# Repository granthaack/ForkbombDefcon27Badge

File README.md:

# ForkbombDefcon27Badge
A badge for Defcon27 in 2019

Brainstorming on the wiki

https://github.com/granthaack/ForkbombDefcon27Badge/wiki

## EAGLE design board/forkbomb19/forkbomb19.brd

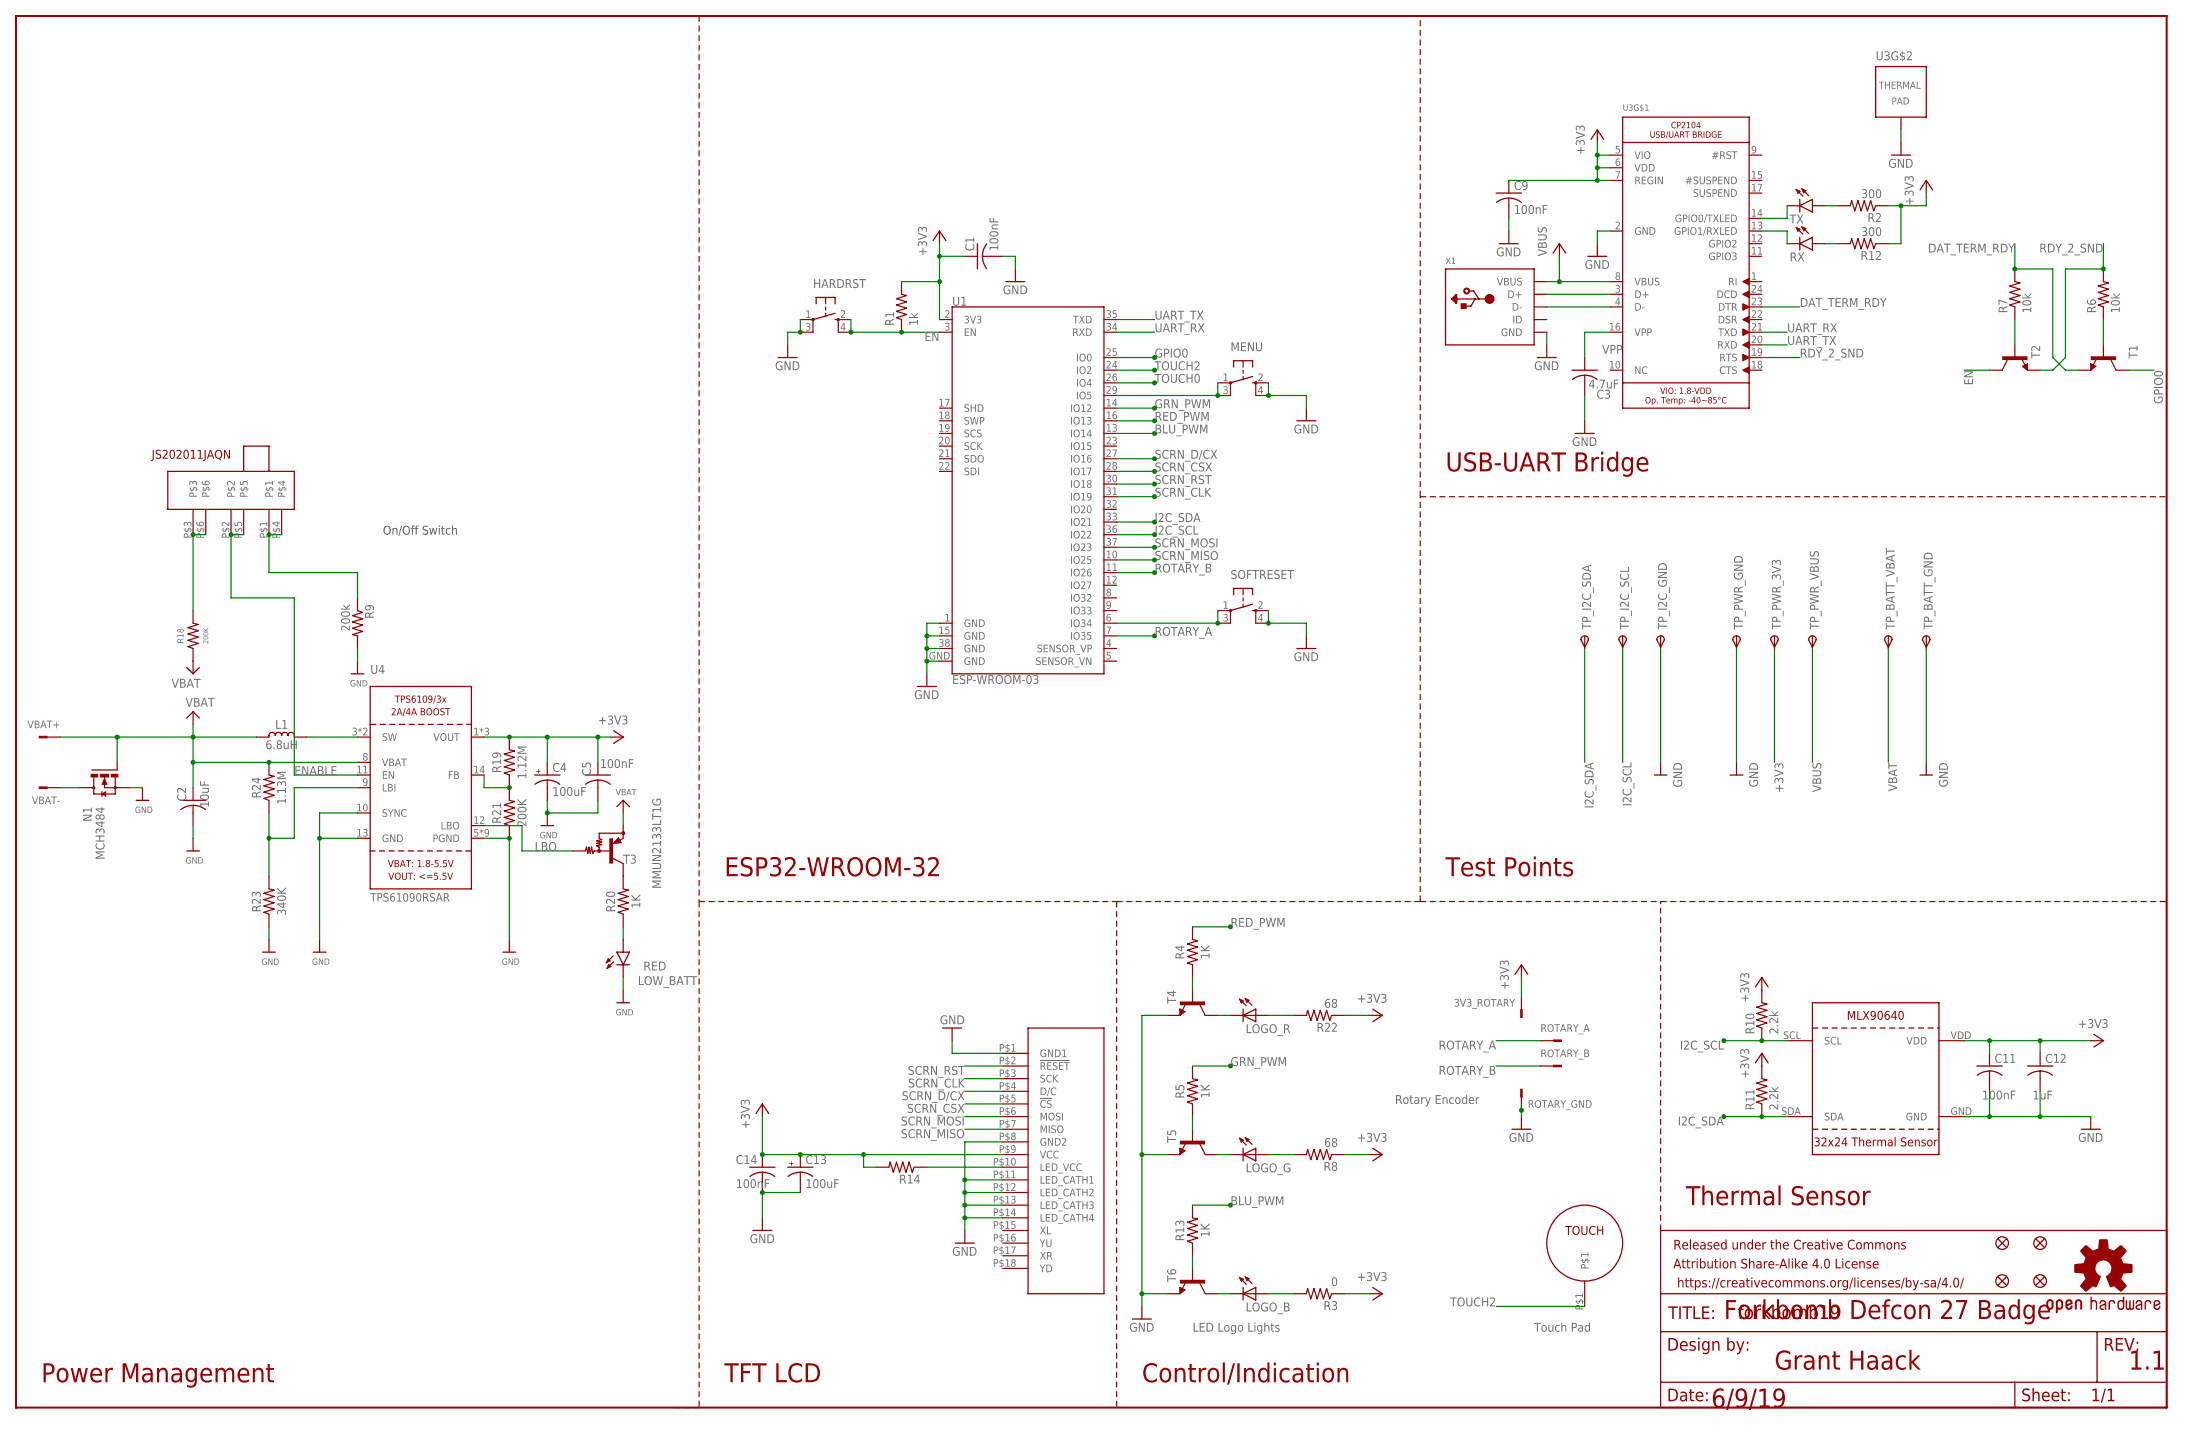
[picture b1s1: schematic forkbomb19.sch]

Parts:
3V3_ROTARY: POT_GND; TSW-101-XX-G-S
C1, C5, C9, C11, C14: 100nF; C0603
C2: 10uF; C1210
C3: 4.7uF; C0805
C4, C13: 100uF; C/6032-28R
C12: 1uF; C0805
FID1, FID2, FID3, FID4: FIDUCIAL_1MM
FRAME1: FRAME-LEDGER; CREATIVE_COMMONS
HARDRST: SPST_TACT-KMR2; KMR2
L1: 6.8uH; INDUCTOR_5X5MM_TDK_VLC5045
LOGO1: OSHW-LOGOS-COPPER; OSHW-LOGO-S_COPPER
LOGO_B: REVERSE_PLCC_LED; PLCC2_LED
LOGO_G: REVERSE_PLCC_LED; PLCC2_LED
LOGO_R: REVERSE_PLCC_LED; PLCC2_LED
LOW_BATT: RED; CHIP-LED0603
MENU: SPST_TACT-KMR2; KMR2
N1: MCH3484
R1: 1k; R0603
R2, R12: 300; R0603
R3: 0; R0805
R4, R5, R13, R20: 1K; R0603
R6, R7: 10k; R0603
R8, R22: 68; R0805
R9: 200k; R0603
R10, R11: 2.2k; R0603
R14: R-US_R1210; R1210
R18, R21: 200K; R0603
R19: 1.12M; R0603
R23: 340K; R0603
R24: 1.13M; R0603
ROTARY_A: POT_SIG; TSW-101-XX-G-S
ROTARY_B: POT_3V3; TSW-101-XX-G-S
ROTARY_GND: POT_GND; TSW-101-XX-G-S
RX: LEDCHIP-LED0603; CHIP-LED0603
SOFTRESET: SPST_TACT-KMR2; KMR2
T1, T2, T4, T5, T6: MMBT3904LT1-NPN-SOT23-BEC; SOT23-BEC
T3: MMUN2133LT1G; SC59-BEC
TOUCH: TOUCHPADTOUCH_BLANK; TOUCH_BLANK
TP_BATT_GND: TPSTP20SQ; TP20SQ
TP_BATT_VBAT: TPSTP20SQ; TP20SQ
TP_I2C_GND, TP_I2C_SCL, TP_I2C_SDA: TPSTP20SQ; TP20SQ
TP_PWR_3V3: TPSTP20SQ; TP20SQ
TP_PWR_GND: TPSTP20SQ; TP20SQ
TP_PWR_VBUS: TPSTP20SQ; TP20SQ
TX: LEDCHIP-LED0603; CHIP-LED0603
U1: ESP-WROOM-03
U3: CP2104; QFN24_4MM_SMSC
U4: TPS61090RSAR; PVQFN-16
U$2: SPI_TFT
U$7: MLX90640
U$8: JS202011JAQN
VBAT+: POT_GND; TSW-101-XX-G-S
VBAT-: POT_GND; TSW-101-XX-G-S
X1: USB_MICRO_20329_V2; 4UCONN_20329_V2

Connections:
+3V3: 3V3_ROTARY.1, C1.1, C4.+, C5.1, C9.1, C11.1, C12.1, C13.+, C14.1, R1.2, R2.1, R3.1, R8.1, R10.2, R11.2, R12.1, R14.2, R19.2, R22.1, TP_PWR_3V3.TP, U1.2 (3V3), U3.5 (VIO), U3.6 (VDD), U3.7 (REGIN), U4.1 (VOUT), U4.15 (VOUT), U4.16 (VOUT), U$2.P$9 (VCC), U$7.VDD
BLU_PWM: R13.2, U1.13 (IO14)
DAT_TERM_RDY: R7.2, T1.E, U3.23 (DTR)
EN: HARDRST.2 (S), HARDRST.4 (S1), R1.1, T2.C, U1.3 (EN)
ENABLE: U4.11 (EN), U$8.P$2, U$8.P$5
GND: C1.2, C2.2, C3.2, C4.-, C5.2, C9.2, C11.2, C12.2, C13.-, C14.2, HARDRST.1, HARDRST.3 (P1), LOW_BATT.C, MENU.2 (S), MENU.4 (S1), N1.S, R9.2, R21.1, R23.1, ROTARY_GND.1, SOFTRESET.2 (S), SOFTRESET.4 (S1), T4.E, T5.E, T6.E, TP_BATT_GND.TP, TP_I2C_GND.TP, TP_PWR_GND.TP, U1.1 (GND), U1.15 (GND), U1.38 (GND), U1.GND, U3.2 (GND), U3.THERM (TP), U4.5 (PGND), U4.6 (PGND), U4.7 (PGND), U4.10 (SYNC), U4.13 (GND), U4.P$18 (PGND), U4.P$19 (PGND), U4.P$20 (PGND), U4.P$21 (PGND), U4.P$22 (PGND), U4.THERMAL (PGND), U$2.P$1 (GND1), U$2.P$8 (GND2), U$2.P$11 (LED_CATH1), U$2.P$12 (LED_CATH2), U$2.P$13 (LED_CATH3), U$2.P$14 (LED_CATH4), U$7.GND, X1.BASE@1 (GND), X1.BASE@2 (GND), X1.GND, X1.SPRT@1 (GND), X1.SPRT@2 (GND), X1.SPRT@3 (GND), X1.SPRT@4 (GND)
GPIO0: T1.C, U1.25 (IO0)
GRN_PWM: R5.2, U1.14 (IO12)
I2C_SCL: R10.1, TP_I2C_SCL.TP, U1.36 (IO22), U$7.SCL
I2C_SDA: R11.1, TP_I2C_SDA.TP, U1.33 (IO21), U$7.SDA
LBO: T3.B, U4.12 (LBO)
MENU: MENU.1, MENU.3 (P1), U1.29 (IO5)
unnamed: R14.1, U$2.P$10 (LED_VCC)
unnamed: SOFTRESET.1, SOFTRESET.3 (P1), U1.6 (IO34)
unnamed: R18.2, U$8.P$3, U$8.P$6
unnamed: LOGO_B.2 (C), T6.C
unnamed: U3.3 (D+), X1.D+
unnamed: U3.4 (D-), X1.D-
unnamed: LOGO_B.1 (A), R3.2
unnamed: LOGO_G.2 (C), T5.C
unnamed: LOGO_R.2 (C), T4.C
unnamed: R5.1, T5.B
unnamed: R13.1, T6.B
unnamed: LOGO_R.1 (A), R22.2
unnamed: R9.1, U$8.P$1, U$8.P$4
unnamed: R4.1, T4.B
unnamed: R7.1, T2.B
unnamed: L1.P$2 (2), U4.3 (SW), U4.4 (SW)
unnamed: R6.1, T1.B
unnamed: N1.D, VBAT-.1
unnamed: RX.C, U3.13 (GPIO1/RXLED)
unnamed: TX.C, U3.14 (GPIO0/TXLED)
unnamed: R2.2, TX.A
unnamed: R12.2, RX.A
unnamed: R23.2, R24.1, U4.9 (LBI)
unnamed: LOW_BATT.A, R20.1
unnamed: R19.1, R21.2, U4.14 (FB)
unnamed: R20.2, T3.C
unnamed: LOGO_G.1 (A), R8.2
RDY_2_SND: R6.2, T2.E, U3.19 (RTS)
RED_PWM: R4.2, U1.16 (IO13)
ROTARY_A: ROTARY_A.1, U1.7 (IO35)
ROTARY_B: ROTARY_B.1, U1.11 (IO26)
SCRN_CLK: U1.31 (IO19), U$2.P$3 (SCK)
SCRN_CSX: U1.28 (IO17), U$2.P$5 (!CS)
SCRN_D/CX: U1.27 (IO16), U$2.P$4 (D/C)
SCRN_MISO: U1.10 (IO25), U$2.P$7 (MISO)
SCRN_MOSI: U1.37 (IO23), U$2.P$6 (MOSI)
SCRN_RST: U1.30 (IO18), U$2.P$2 (!RESET)
TOUCH0: U1.26 (IO4)
TOUCH2: TOUCH.P$1, U1.24 (IO2)
UART_RX: U1.34 (RXD), U3.21 (TXD)
UART_TX: U1.35 (TXD), U3.20 (RXD)
VBAT: C2.1, L1.P$1 (1), N1.G, R18.1, R24.2, T3.E, TP_BATT_VBAT.TP, U4.8 (VBAT), VBAT+.1
VBUS: TP_PWR_VBUS.TP, U3.8 (VBUS), X1.VBUS
VPP: C3.1, U3.16 (VPP)

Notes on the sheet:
On/Off Switch
Power Management
TFT LCD
Thermal Sensor
ESP32-WROOM-32
USB-UART Bridge
Control/Indication
Forkbomb Defcon 27 Badge
Grant Haack
6/9/19
1.1
LED Logo Lights
Touch Pad
Rotary Encoder
Test Points

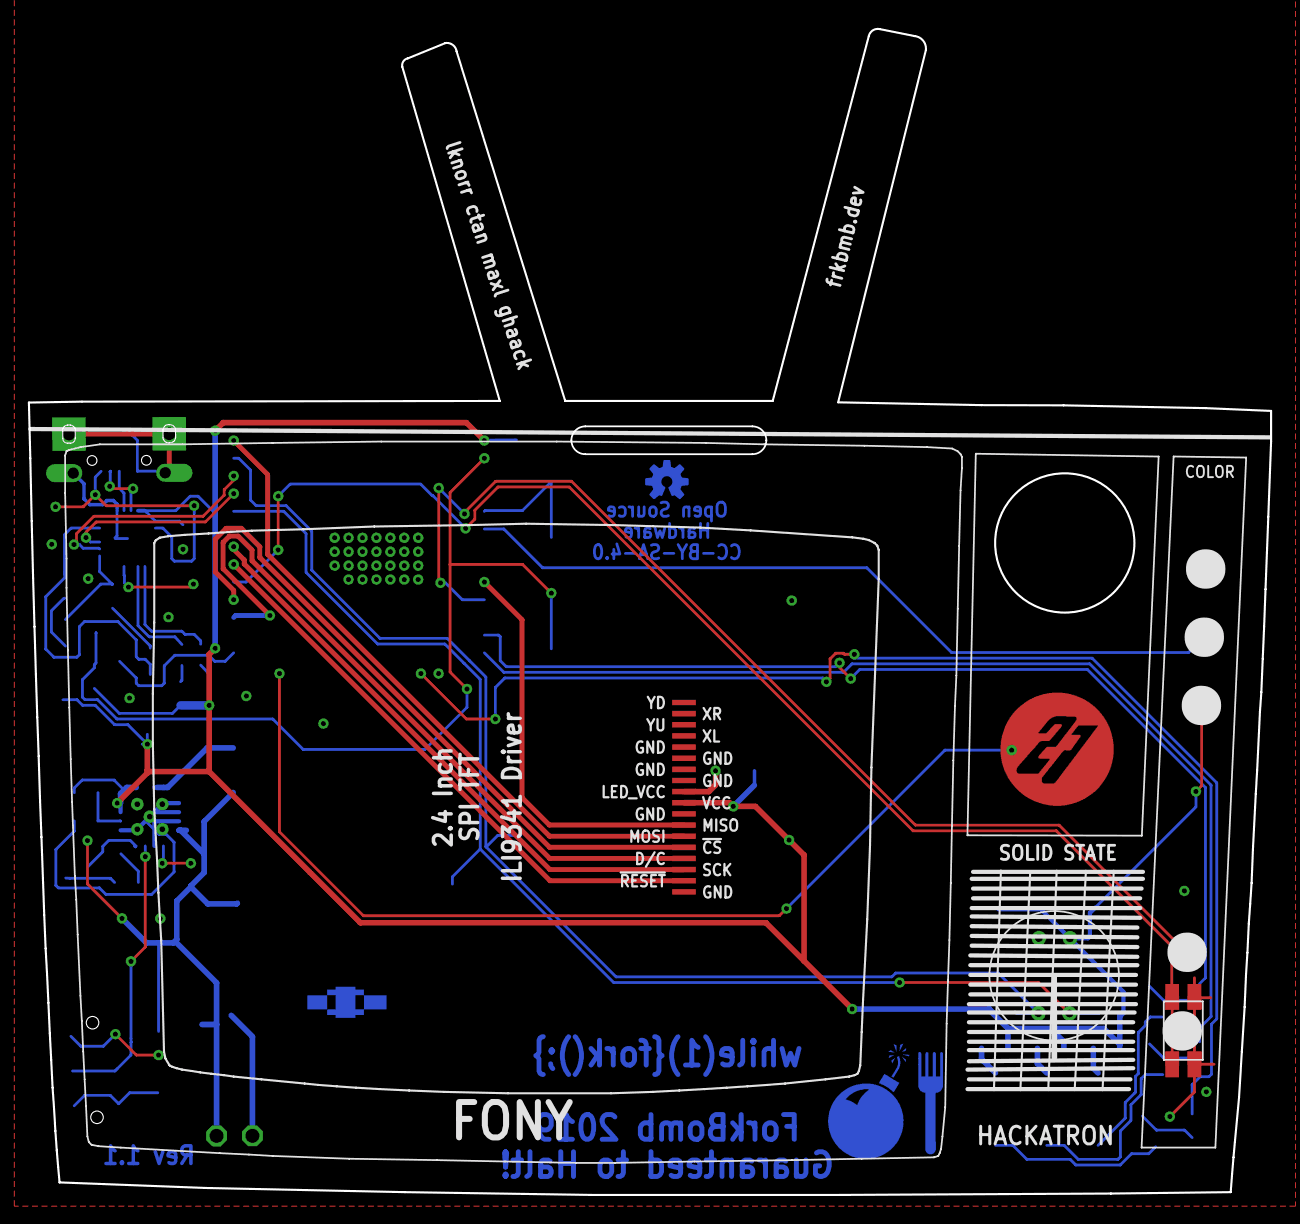
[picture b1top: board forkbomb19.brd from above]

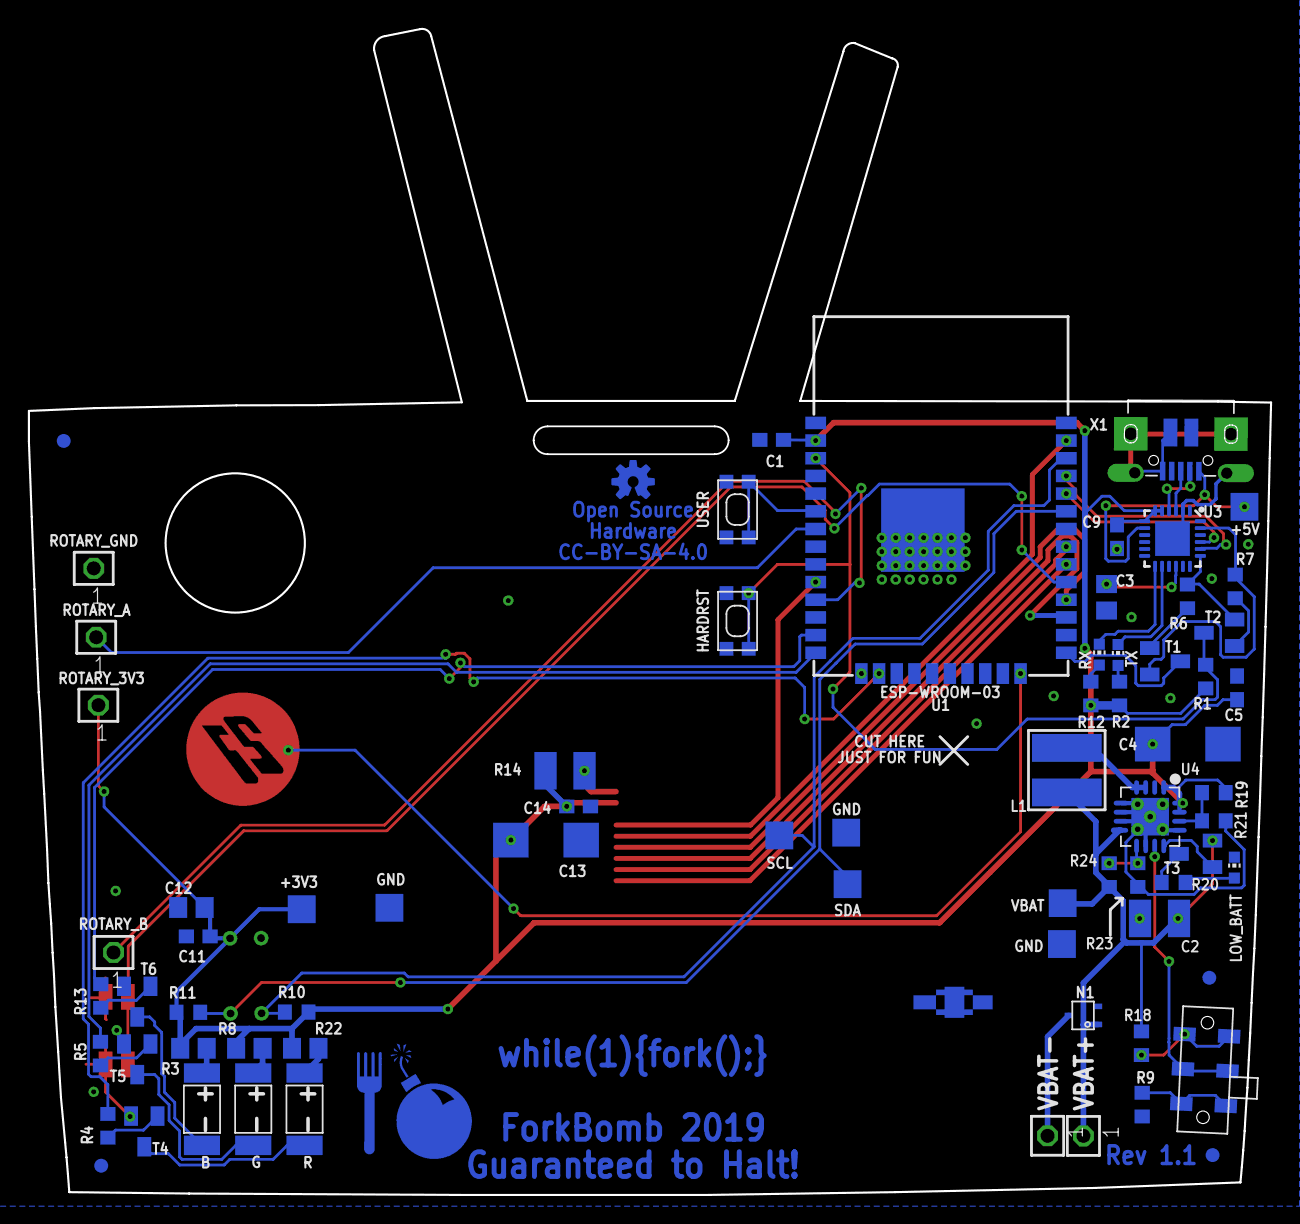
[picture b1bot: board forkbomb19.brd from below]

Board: 2 copper layers, 89.2 x 83.7 mm, 76 parts (71 on the bottom side), 55 nets.

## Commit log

2019-01-03 Initial I2C thermal camera driver
2019-01-03 Clean main
2019-01-05 started work on the board design
2019-01-05 added IR sensor and LED driver to board
2019-01-06 drew the tv and started placing stuff
2019-01-20 more layout work on the board
2019-01-20 better layout, made room for AA's
2019-01-21 more layout work, trying to remove excess vias
2019-01-23 silkscreen placement
2019-01-24 created screen
2019-01-25 added touch pad
2019-01-25 wrote a simple i2c register read function
2019-01-25 started work on a spi ili9341 library
2019-01-26 more work on SPI LCD driver
2019-01-28 tested LCD functions, seem to be working
2019-01-30 starting to work on LCD screen drawing task
2019-01-31 starting work on basic networking stuff and menuconfig options
2019-02-02 started work on rpi host
2019-02-02 small board modifications
2019-02-03 working on bandwidth tester
2019-02-03 Got the bandwidth tester working
2019-02-24 started basic library for the thermal sensor
2019-02-25 basic thermal camera demo working, no interpolation offloading
2019-02-25 can't pass data into a freertos function
2019-02-25 starting to lose it with this freertos passing nonsense
2019-03-01 moving to lithium batteries
2019-04-01 moved thing to tasks, but introduced screen tearing
2019-04-01 fixed screen tearing but it's a hack
2019-04-01 switched to using mutex
2019-04-30 added interpolation
2019-06-06 added new thermal sensor part
2019-06-06 added thermal sensor to the board
2019-06-07 TODO: -Make sure all components on the BOM are in stock -Find a potentiometer that fits -Find knobs for the pot -Remake the on/off switch footprint/make sure it's still in stock. Maybe change to side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
2019-06-08 footprint pretty much done, needs cleanup
2019-06-08 small cleanup
2019-06-09 made a BOM, cleaned up the board, added a styles 27 button
2019-06-09 cleaning up board and schematic
2019-06-10 performing board review
2019-06-10 TODO: Add rotary encoder, add another button, pwm the lights
2019-06-11 added PWM control for LEDs, swapped the potentiometer for a rotary encoder, and added a menu button
2019-06-11 cleaned up board, routed a couple signals
2019-06-16 ready for board sign off
2019-06-30 working on rev 1.1
2019-06-30 started doing layout for rev 1.1
2019-07-01 finished rev 1.1
2019-07-21 got an image on the screen
2019-07-21 interpolation is almost working

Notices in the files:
board/forkbomb19/forkbomb19.brd:
CC-BY-SA-4.0
parts and their libraries:
microbuilder: This work is placed in the public domain, and may be freely used for commercial and non-commercial work with the following conditions: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
SparkFun-Aesthetics: Licensing: Creative Commons ShareAlike 4.0 International - https://creativecommons.org/licenses/by-sa/4.0
